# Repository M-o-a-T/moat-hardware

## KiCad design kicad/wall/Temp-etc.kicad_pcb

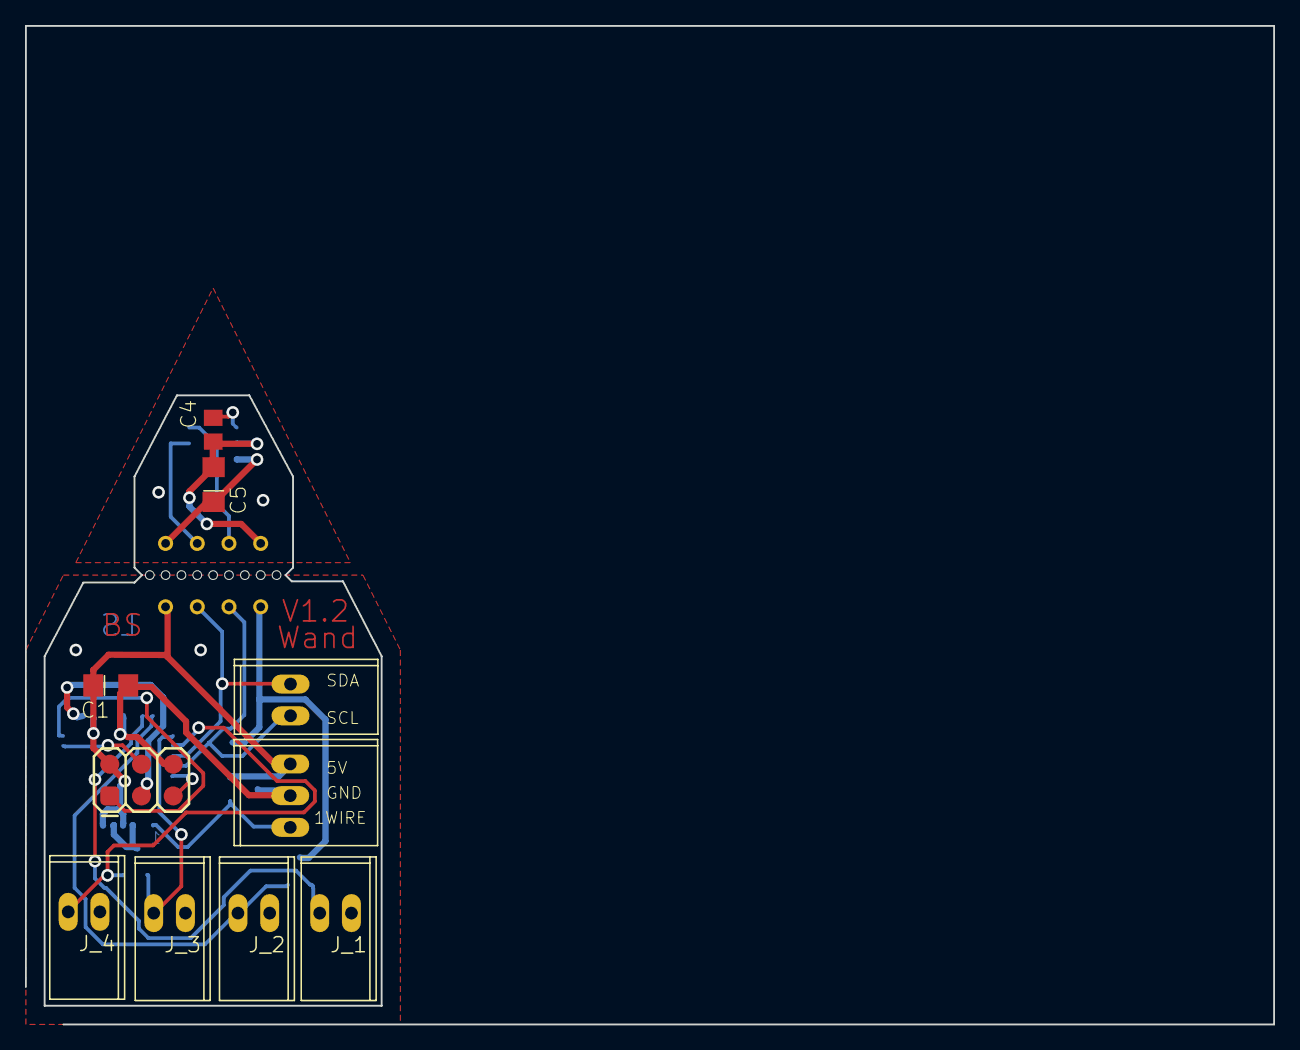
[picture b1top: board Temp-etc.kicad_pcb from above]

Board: 2 copper layers, 100.0 x 80.0 mm, 17 parts (0 on the bottom side), 18 nets.

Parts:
C1, C5: CP1206
C4: CC0805; C0805
D1, D4, D5, D6: ESD_DIODES; SOT23
IC1: MEGA8-PTQFP; TQFP32-08
JP1: PINHD-1X2LEVER; 1X02_GN
JP2: PINHD-2X4BRIDGE; 2X04_BRIDGE
J_1, J_2, J_3, J_4: PINHD-1X2LEVER; 1X02_GN
LEVER1: PINHD-1X3LEVER; 1X03_GN
U$1: AVR_SPI_PRG_6PAD; 2X3_PAD
U$2: CHIPCAP2

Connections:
/B1: D4.1, IC1.23, J_1.2
/B2: D4.2, IC1.24, J_2.2
/B3: D5.1, IC1.25, J_3.2
/B4: D5.2, IC1.26, J_4.2
/SCL: D6.2, IC1.28, JP1.2, JP2.4
/SDA: D6.1, IC1.27, JP1.1, JP2.6
GND: C1.-, D1.3, D4.3, D5.3, D6.3, IC1.3, IC1.5, IC1.21, JP2.2, J_1.1, J_2.1, J_3.1, J_4.1, LEVER1.2, U$1.P$6
unnamed: C4.1, C5.-, JP2.1, U$2.P$6
unnamed: C4.2, U$2.P$5
unnamed: C5.+, JP2.7, U$2.P$7
unnamed: D1.1, IC1.1, LEVER1.3
unnamed: IC1.15, U$1.P$4
unnamed: IC1.16, U$1.P$1
unnamed: IC1.17, U$1.P$3
unnamed: IC1.29, U$1.P$5
unnamed: JP2.3, U$2.P$4
unnamed: JP2.5, U$2.P$3
VCC: C1.+, D1.2, IC1.4, IC1.6, IC1.18, JP2.8, LEVER1.1, U$1.P$2

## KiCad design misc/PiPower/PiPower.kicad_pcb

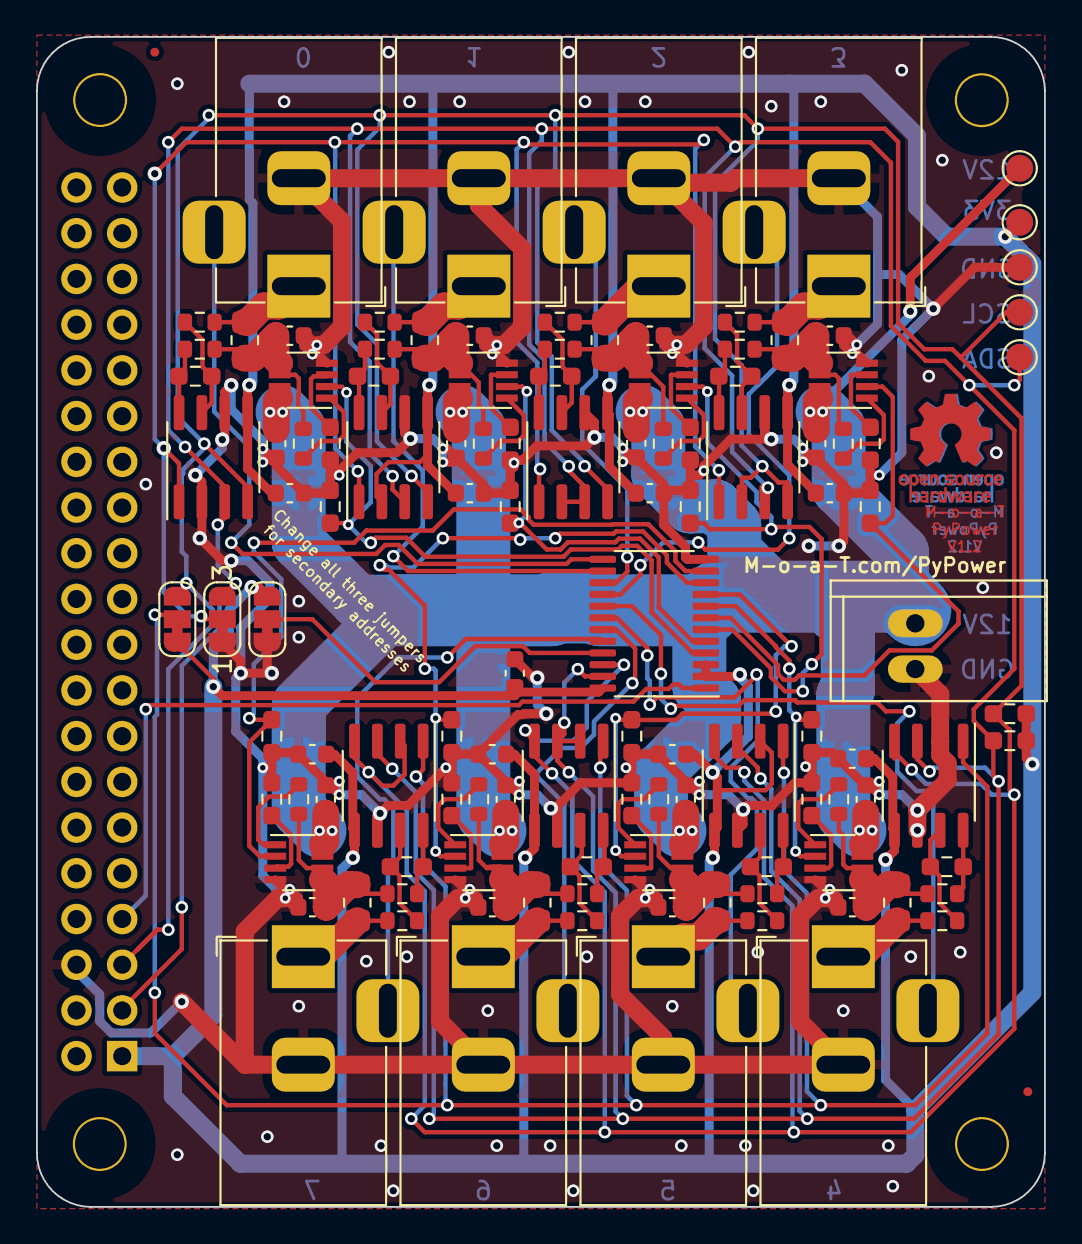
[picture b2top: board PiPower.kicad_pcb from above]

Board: 2 copper layers, 56.0 x 65.0 mm, 122 parts (1 on the bottom side), 73 nets.

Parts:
C1, C3, C6, C7, C9, C12, C13, C15, C17, C23, C26, C27, C30, C32, C33, C36: 10µF; C_0603_1608Metric
C2, C8, C10, C11, C18, C28, C29, C31: 0; R_0603_1608Metric_Pad0.98x0.95mm_HandSolder
C4, C14, C16, C19, C24, C34, C35, C37, C41: .1µF; C_0603_1608Metric
C5, C20, C21, C22, C25, C38, C39, C40: 1µ; R_0603_1608Metric_Pad0.98x0.95mm_HandSolder
H1, H2, H3, H4: 3mm_Mounting_Hole; NPTH_3mm_ID
J1: Raspberry_Pi_2_3; PinSocket_2x20_P2.54mm_Vertical
J2: Power; 1X02_GN
J3: Out 0; Barrel Jack locking
J4: Out 1; Barrel Jack locking
J5: Out 2; Barrel Jack locking
J6: Out 3; Barrel Jack locking
J7: Out 4; Barrel Jack locking
J8: Out 5; Barrel Jack locking
J9: Out 7; Barrel Jack locking
J10: Out 6; Barrel Jack locking
JP1, JP2, JP3: Jumper_3_Bridged12; SolderJumper-3_P1.3mm_Bridged12_RoundedPad1.0x1.5mm_NumberL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
R1, R5, R6, R7, R17, R21, R22, R23: 22; R_0603_1608Metric
R2, R4, R8, R10, R11, R13, R14, R16, R18, R20, R24, R25, R28, R29, R30, R32: 10; R_0603_1608Metric
R3, R9, R12, R15, R19, R26, R27, R31: .1; R_0805_2012Metric_Pad1.20x1.40mm_HandSolder
R33, R34: 1k; R_0603_1608Metric_Pad0.98x0.95mm_HandSolder
R35, R36, R37, R38, R39, R40, R41, R42: 10k; R_0603_1608Metric_Pad0.98x0.95mm_HandSolder
TP1, TP2, TP3, TP4, TP5: TestPoint; TestPoint_Pad_D1.5mm
U1, U3, U4, U5, U8, U11, U12, U13: MP5014A; TSOT-23-8
U2, U6, U7, U9, U10, U14, U15, U16: INA219AxD; SOIC-8_3.9x4.9mm_P1.27mm
U17: PCAL6416APW; TSSOP-24_4.4x7.8mm_P0.65mm

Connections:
+3V3: C4.1, C14.1, C16.1, C19.1, C24.1, C34.1, C35.1, C37.1, C41.1, J1.1 (3V3), JP2.1 (A), JP3.3 (B), R33.2, R34.2, TP2.1, U2.5 (VS), U6.2 (A0), U6.5 (VS), U7.5 (VS), U9.5 (VS), U10.5 (VS), U14.2 (A0), U14.5 (VS), U15.5 (VS), U16.5 (VS), U17.2 (VDD_I2C), U17.3 (~RESET), U17.24 (VDD_P)
+12V: C1.1, C6.1, C7.1, C9.1, C13.1, C26.1, C27.1, C30.1, J2.1, TP3.1, U1.7 (Vcc), U1.8 (Vcc), U3.7 (Vcc), U3.8 (Vcc), U4.7 (Vcc), U4.8 (Vcc), U5.7 (Vcc), U5.8 (Vcc), U8.7 (Vcc), U8.8 (Vcc), U11.7 (Vcc), U11.8 (Vcc), U12.7 (Vcc), U12.8 (Vcc), U13.7 (Vcc), U13.8 (Vcc)
/The other seven/V12O1: J4.1, R9.2, R11.2
/The other seven/V12O2: J5.1, R12.2, R14.2
/The other seven/V12O3: J6.1, R15.2, R16.2
/The other seven/V12O4: J7.1, R19.2, R20.2
/The other seven/V12O5: J8.1, R26.2, R28.2
/The other seven/V12O6: J10.1, R31.2, R32.2
/The other seven/V12O7: J9.1, R27.2, R29.2
/The other seven/V12P1: C12.1, R5.2, R8.2, R9.1, U3.5 (Source), U3.6 (Source)
/The other seven/V12P2: C15.1, R6.2, R10.2, R12.1, U4.5 (Source), U4.6 (Source)
/The other seven/V12P3: C17.1, R7.2, R13.2, R15.1, U5.5 (Source), U5.6 (Source)
/The other seven/V12P4: C23.1, R17.2, R18.2, R19.1, U8.5 (Source), U8.6 (Source)
/The other seven/V12P5: C32.1, R21.2, R24.2, R26.1, U11.5 (Source), U11.6 (Source)
/The other seven/V12P6: C36.1, R23.2, R30.2, R31.1, U13.5 (Source), U13.6 (Source)
/V12O0: J3.1, R3.2, R4.2
/V12P0: C3.1, R1.2, R2.2, R3.1, U1.5 (Source), U1.6 (Source)
ENA0: R42.2, U1.2 (Enable/Fault), U17.4 (P0_0)
ENA1: R41.2, U3.2 (Enable/Fault), U17.5 (P0_1)
ENA2: R40.2, U4.2 (Enable/Fault), U17.6 (P0_2)
ENA3: R39.2, U5.2 (Enable/Fault), U17.7 (P0_3)
ENA4: R38.2, U8.2 (Enable/Fault), U17.8 (P0_4)
ENA5: R37.2, U11.2 (Enable/Fault), U17.9 (P0_5)
ENA6: R36.2, U13.2 (Enable/Fault), U17.10 (P0_6)
ENA7: R35.2, U12.2 (Enable/Fault), U17.11 (P0_7)
GND: C1.2, C2.2, C3.2, C4.2, C6.2, C7.2, C8.2, C9.2, C10.2, C11.2, C12.2, C13.2, C14.2, C15.2, C16.2, C17.2, C18.2, C19.2, C23.2, C24.2, C26.2, C27.2, C28.2, C29.2, C30.2, C31.2, C32.2, C33.2, C34.2, C35.2, C36.2, C37.2, C41.2, J1.6 (GND), J2.2, J3.2, J4.2, J5.2, J6.2, J7.2, J8.2, J9.2, J10.2, JP1.1 (A), JP3.1 (A), R35.1, R36.1, R37.1, R38.1, R39.1, R40.1, R41.1, R42.1, TP1.1, U1.4 (GND), U2.2 (A0), U2.6 (GND), U3.4 (GND), U4.4 (GND), U5.4 (GND), U6.6 (GND), U7.6 (GND), U8.4 (GND), U9.6 (GND), U10.2 (A0), U10.6 (GND), U11.4 (GND), U12.4 (GND), U13.4 (GND), U14.6 (GND), U15.6 (GND), U16.6 (GND), U17.12 (VSS)
unnamed: C2.1, U1.3 (DV/DT)
unnamed: C5.1, R2.1, U2.8 (IN+)
unnamed: C5.2, R4.1, U2.7 (IN-)
unnamed: C8.1, U3.3 (DV/DT)
unnamed: C10.1, U4.3 (DV/DT)
unnamed: C11.1, U5.3 (DV/DT)
unnamed: C18.1, U8.3 (DV/DT)
unnamed: C20.1, R8.1, U6.8 (IN+)
unnamed: C20.2, R11.1, U6.7 (IN-)
unnamed: C21.1, R10.1, U7.8 (IN+)
unnamed: C21.2, R14.1, U7.7 (IN-)
unnamed: C22.1, R13.1, U9.8 (IN+)
unnamed: C22.2, R16.1, U9.7 (IN-)
unnamed: C25.1, R18.1, U10.8 (IN+)
unnamed: C25.2, R20.1, U10.7 (IN-)
unnamed: C28.1, U11.3 (DV/DT)
unnamed: C29.1, U12.3 (DV/DT)
unnamed: C31.1, U13.3 (DV/DT)
unnamed: C33.1, R22.2, R25.2, R27.1, U12.5 (Source), U12.6 (Source)
unnamed: C38.1, R24.1, U14.8 (IN+)
unnamed: C38.2, R28.1, U14.7 (IN-)
unnamed: C39.1, R25.1, U15.8 (IN+)
unnamed: C39.2, R29.1, U15.7 (IN-)
unnamed: C40.1, R30.1, U16.8 (IN+)
unnamed: C40.2, R32.1, U16.7 (IN-)
unnamed: J1.7 (GCLK0/GPIO4), U17.1 (~INT)
unnamed: R1.1, U1.1 (I-Limit)
unnamed: R5.1, U3.1 (I-Limit)
unnamed: R6.1, U4.1 (I-Limit)
unnamed: R7.1, U5.1 (I-Limit)
unnamed: R17.1, U8.1 (I-Limit)
unnamed: R21.1, U11.1 (I-Limit)
unnamed: R22.1, U12.1 (I-Limit)
unnamed: R23.1, U13.1 (I-Limit)
SCL: J1.5 (SCL/GPIO3), JP2.3 (B), R33.1, TP4.1, U2.4 (SCL), U6.4 (SCL), U7.4 (SCL), U9.2 (A0), U9.4 (SCL), U10.4 (SCL), U14.4 (SCL), U15.2 (A0), U15.4 (SCL), U16.4 (SCL), U17.22 (SCL)
SDA: J1.3 (SDA/GPIO2), JP1.3 (B), R34.1, TP5.1, U2.3 (SDA), U6.3 (SDA), U7.2 (A0), U7.3 (SDA), U9.3 (SDA), U10.3 (SDA), U14.3 (SDA), U15.3 (SDA), U16.2 (A0), U16.3 (SDA), U17.23 (SDA)
SEL: JP3.2 (C), U17.21 (ADDR)
SEL03: JP1.2 (C), U2.1 (A1), U6.1 (A1), U7.1 (A1), U9.1 (A1)
SEL47: JP2.2 (C), U10.1 (A1), U14.1 (A1), U15.1 (A1), U16.1 (A1)
SENS0: J3.3, U17.13 (P1_0)
SENS1: J4.3, U17.14 (P1_1)
SENS2: J5.3, U17.15 (P1_2)
SENS3: J6.3, U17.16 (P1_3)
SENS4: J7.3, U17.17 (P1_4)
SENS5: J8.3, U17.18 (P1_5)
SENS6: J10.3, U17.19 (P1_6)
SENS7: J9.3, U17.20 (P1_7)

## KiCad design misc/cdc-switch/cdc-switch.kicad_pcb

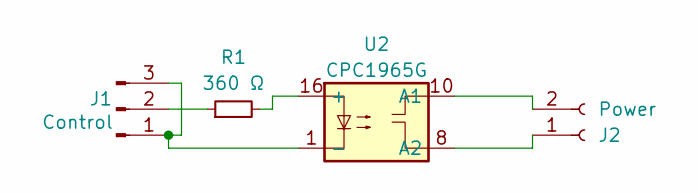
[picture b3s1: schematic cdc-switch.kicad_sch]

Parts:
J1: Control; PinHeader_1x03_P2.54mm_Horizontal
J2: Power; Conn_P5.1mm_2_Molex
R1: R_220_0603; R_0603_1608Metric_Pad0.98x0.95mm_HandSolder
U2: CPC1965G; DIL16-CPC1965G

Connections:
unnamed: J1.1, J1.3, U2.1 (-)
unnamed: J1.2, R1.1
unnamed: J2.1, U2.8 (A2)
unnamed: J2.2, U2.10 (A1)
unnamed: R1.2, U2.16 (+)

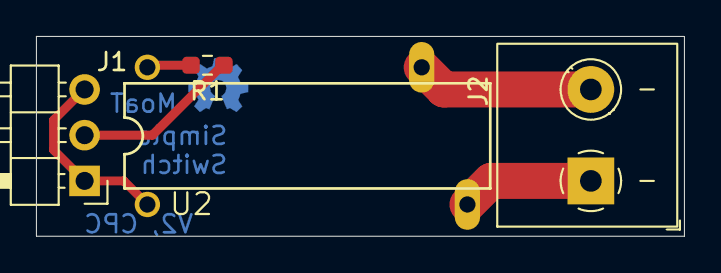
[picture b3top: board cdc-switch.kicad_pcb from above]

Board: 2 copper layers, 36.0 x 11.1 mm, 4 parts (0 on the bottom side), 5 nets.

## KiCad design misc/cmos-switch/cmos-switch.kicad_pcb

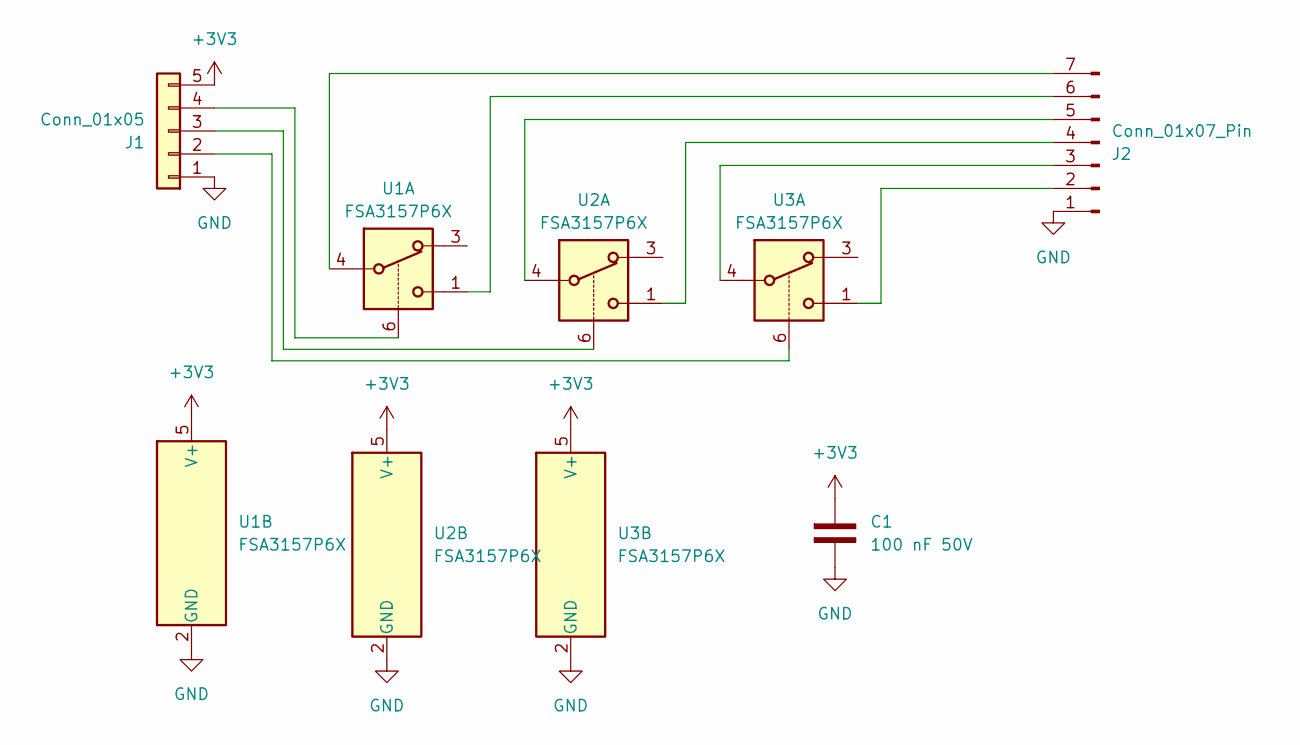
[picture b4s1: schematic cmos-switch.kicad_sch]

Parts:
C1: CP_100n_50V_0603; C_0603_1608Metric; LCSC C14663
J1: Conn_01x05; PinHeader_1x05_P2.54mm_Vertical
J2: Conn_01x07_Pin; PinHeader_1x07_P2.54mm_Vertical
U1, U2, U3: FSA3157P6X; SOT-363_SC-70-6

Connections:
+3V3: C1.1, J1.5, U1.5 (V+), U2.5 (V+), U3.5 (V+)
GND: C1.2, J1.1, J2.1, U1.2 (GND), U2.2 (GND), U3.2 (GND)
unnamed: J1.2, U3.6
unnamed: J1.3, U2.6
unnamed: J1.4, U1.6
unnamed: J2.2, U3.1
unnamed: J2.3, U3.4
unnamed: J2.4, U2.1
unnamed: J2.5, U2.4
unnamed: J2.6, U1.1
unnamed: J2.7, U1.4

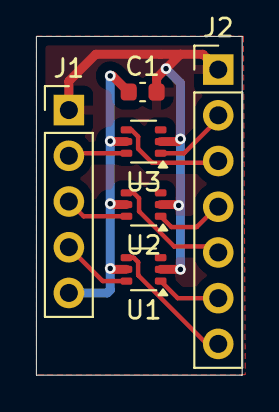
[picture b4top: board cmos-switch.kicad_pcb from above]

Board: 2 copper layers, 11.4 x 18.8 mm, 6 parts (0 on the bottom side), 11 nets.

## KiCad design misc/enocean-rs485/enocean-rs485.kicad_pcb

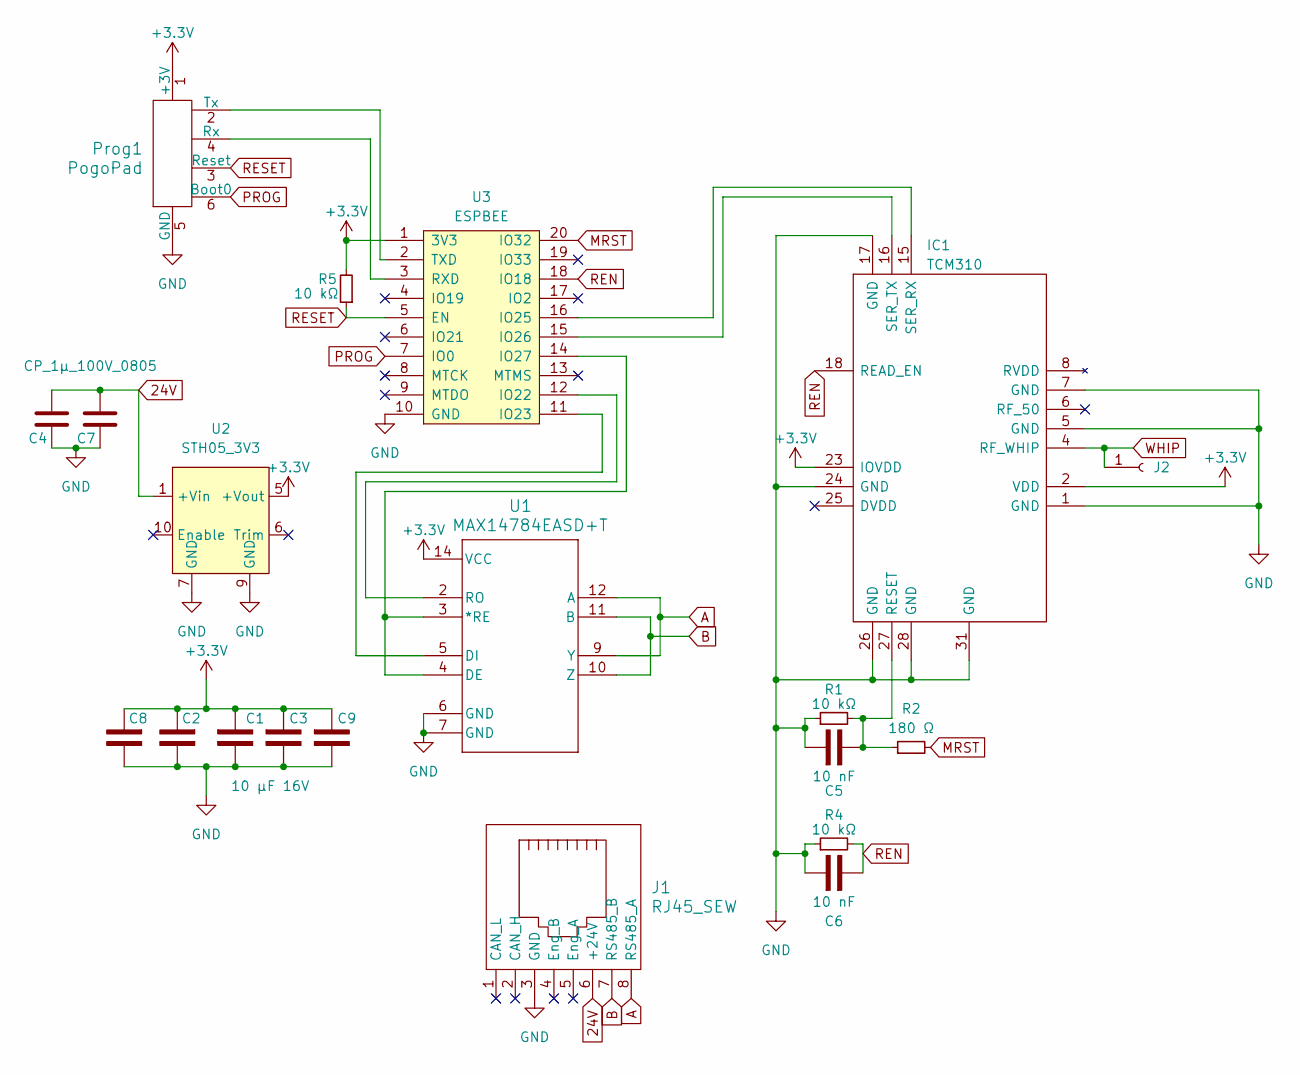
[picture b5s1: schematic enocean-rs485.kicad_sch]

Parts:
C1, C2, C3, C8, C9: CP_10µ_16V_0603; C_0603_1608Metric
C4, C7: CP_1µ_100V_0805; R_0805_2012Metric; Farnell 3243166
C5, C6: C_10n_0603; C_0603_1608Metric
IC1: TCM310; Manufacturer_Part_Number TCM310
J1: RJ45_SEW; RJ45-NO-SHIELD
J2: Conn_01x01_Female; Pin_D0.7mm_L6.5mm_W1.8mm_FlatFork
Prog1: PogoPad; 2X3_PAD
R1, R4, R5: R_10k_0603; R_0603_1608Metric
R2: R_180_0603; R_0603_1608Metric
U1: MAX14784EASD+T; SO-16_3.9x9.9mm_P1.27mm
U2: STH05_3V3; STH05; Farnell 3212470
U3: ESPBEE

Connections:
24V: C4.1, C7.1, J1.6 (+24V), U2.1 (+Vin)
+3V3: C1.1, C2.1, C3.1, C8.1, C9.1, IC1.2 (VDD), IC1.23 (IOVDD), Prog1.1 (+3V), R5.2, U1.14 (VCC), U2.5 (+Vout), U3.1 (3V3)
A: J1.8 (RS485_A), U1.9 (Y), U1.12 (A)
B: J1.7 (RS485_B), U1.10 (Z), U1.11 (B)
GND: C1.2, C2.2, C3.2, C4.2, C5.1, C6.1, C7.2, C8.2, C9.2, IC1.1 (GND), IC1.5 (GND), IC1.7 (GND), IC1.17 (GND), IC1.24 (GND), IC1.26 (GND), IC1.28 (GND), IC1.31 (GND), J1.3 (GND), Prog1.5 (GND), R1.1, R4.1, U1.6 (GND), U1.7 (GND), U2.7 (GND), U2.9 (GND), U3.10 (GND)
MRST: R2.2, U3.20 (IO32)
unnamed: C5.2, IC1.27 (RESET), R1.2, R2.1
unnamed: IC1.15 (SER_RX), U3.16 (IO25)
unnamed: IC1.16 (SER_TX), U3.15 (IO26)
unnamed: Prog1.4 (Rx), U3.3 (RXD)
unnamed: Prog1.2 (Tx), U3.2 (TXD)
unnamed: U1.3 (*RE), U1.4 (DE), U3.14 (IO27)
unnamed: U1.5 (DI), U3.11 (IO23)
unnamed: U1.2 (RO), U3.12 (IO22)
PROG: Prog1.6 (Boot0), U3.7 (IO0)
REN: C6.2, IC1.18 (READ_EN), R4.2, U3.18 (IO18)
RESET: Prog1.3 (Reset), R5.1, U3.5 (EN)
WHIP: IC1.4 (RF_WHIP), J2.1

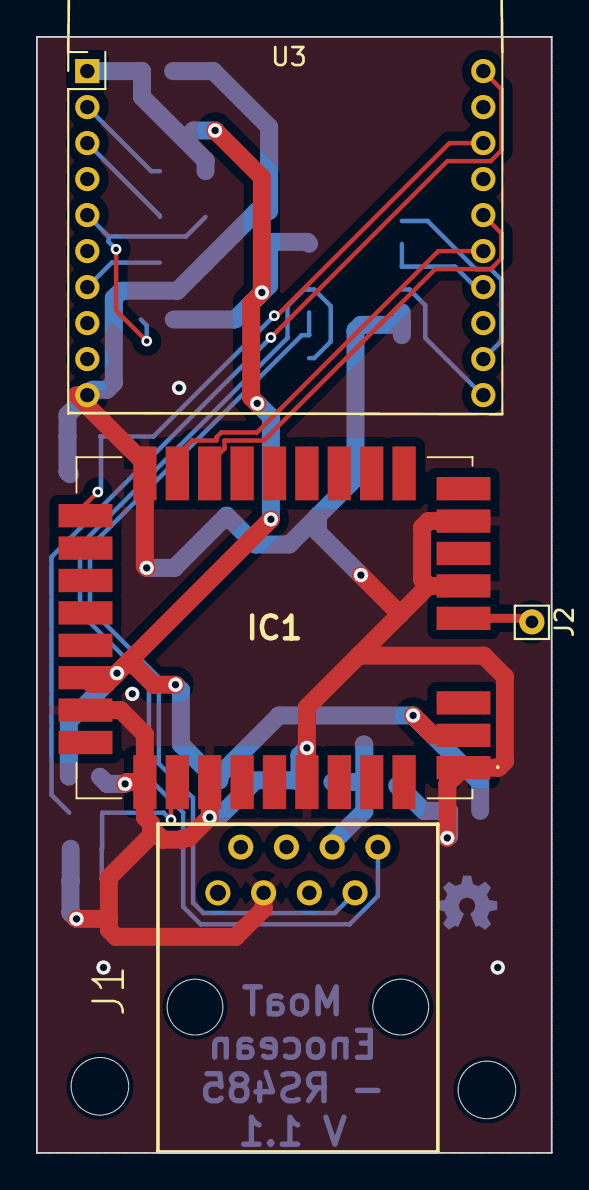
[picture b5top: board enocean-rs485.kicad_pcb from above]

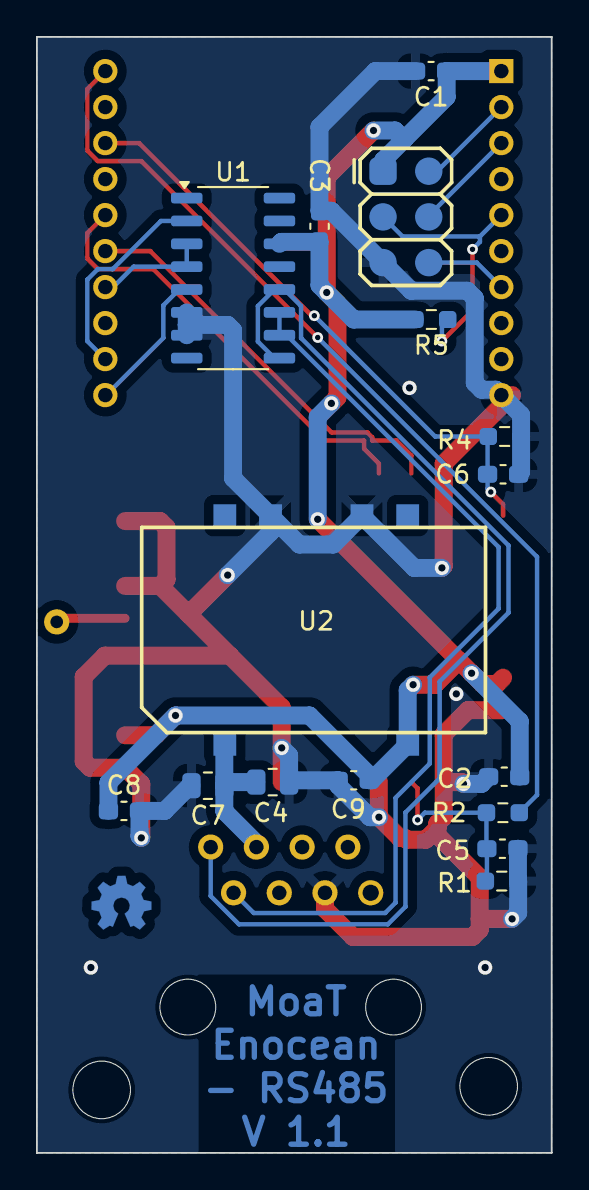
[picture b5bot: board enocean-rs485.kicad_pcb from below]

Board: 2 copper layers, 28.6 x 62.0 mm, 20 parts (16 on the bottom side), 18 nets.

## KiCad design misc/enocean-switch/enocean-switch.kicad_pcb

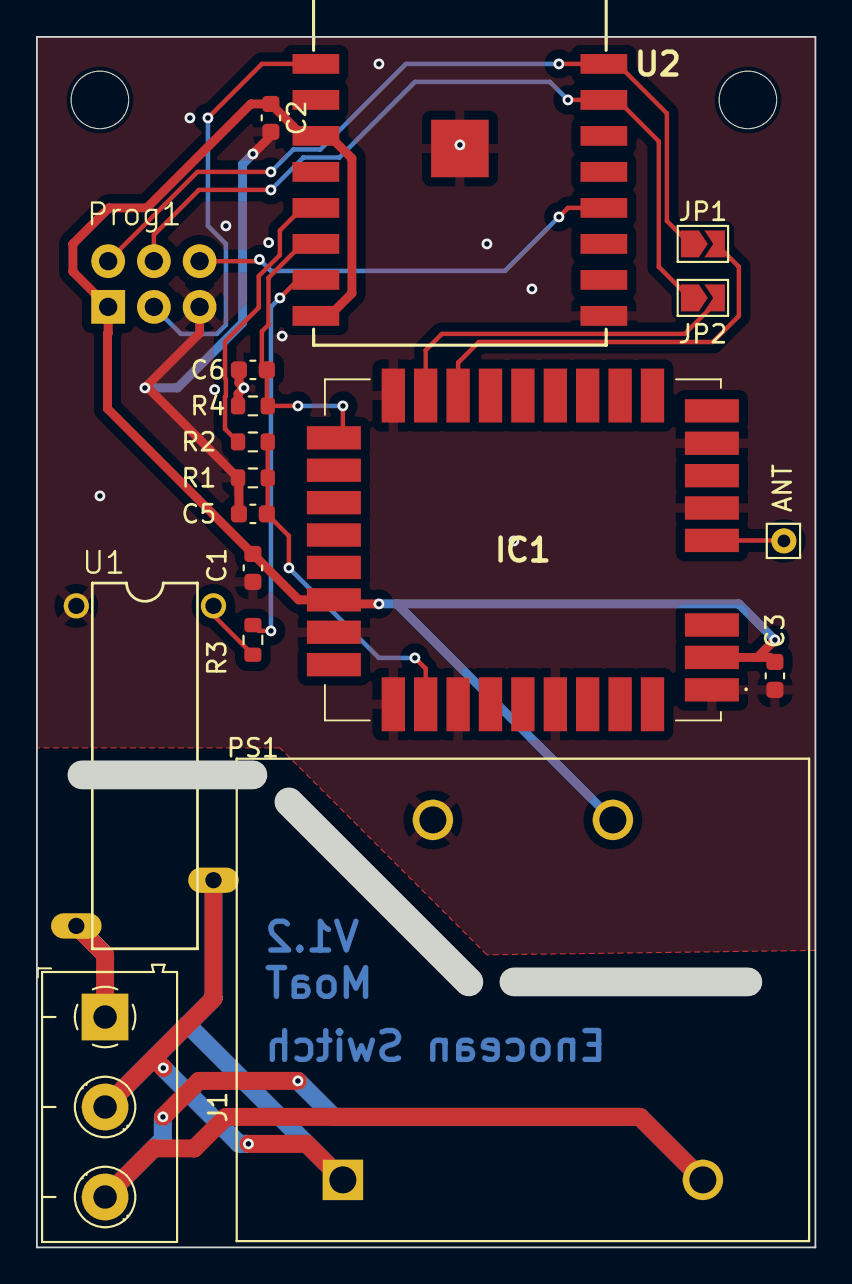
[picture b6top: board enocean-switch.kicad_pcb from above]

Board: 2 copper layers, 43.2 x 67.2 mm, 18 parts (0 on the bottom side), 17 nets.

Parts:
C1, C2, C3: CP_10µ_16V_0603; C_0603_1608Metric
C5, C6: C_10n_0603; C_0603_1608Metric
IC1: TCM310
J1: Conn_01x03_Female; Conn_P5.0mm_3_Lumberg
J2: Conn_01x01_Female; Pin_D0.7mm_L6.5mm_W1.8mm_FlatFork
JP1, JP2: Jumper_NC; SolderJumper-2_P1.3mm_Open_TrianglePad1.0x1.5mm
PS1: VTX-214-003-103; VTX-214
Prog1: PogoPad; 2X3-NS
R1, R4: R_10k_0603; R_0603_1608Metric
R2: R_180_0603; R_0603_1608Metric
R3: R_220_0603; R_0603_1608Metric
U1: CPC1965G; DIL16-CPC1965G
U2: ESP-12S

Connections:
+3V3: C1.1, C2.1, C3.1, IC1.2 (VDD), IC1.23 (IOVDD), PS1.3 (DC+), Prog1.1 (+3V), U2.3 (EN), U2.8 (VCC)
GND: C1.2, C2.2, C3.2, C5.1, C6.1, IC1.1 (GND), IC1.5 (GND), IC1.7 (GND), IC1.17 (GND), IC1.24 (GND), IC1.26 (GND), IC1.28 (GND), IC1.31 (GND), PS1.4 (DC-), Prog1.5 (GND), R1.1, R4.1, U1.1 (-), U2.9 (GND), U2.P$1 (GND)
MRST: R2.2, U2.5 (IO14)
unnamed: C5.2, IC1.27 (RESET), R1.2, R2.1
unnamed: IC1.15 (SER_RX), JP1.2
unnamed: IC1.16 (SER_TX), JP2.2
unnamed: J1.1, U1.8 (A2)
unnamed: J1.2, PS1.1 (L), U1.10 (A1)
unnamed: J1.3, PS1.2 (N)
unnamed: Prog1.3 (Reset), U2.1 (RST)
unnamed: JP2.1, Prog1.4 (Rx), U2.15 (RXD0)
unnamed: JP1.1, Prog1.2 (Tx), U2.16 (TXD0)
unnamed: R3.2, U1.16 (+)
PROG: Prog1.6 (Boot0), U2.12 (IO0)
REN: C6.2, IC1.18 (READ_EN), R4.2, U2.6 (IO12)
SIG: R3.1, U2.7 (IO13)
WHIP: IC1.4 (RF_WHIP), J2.1

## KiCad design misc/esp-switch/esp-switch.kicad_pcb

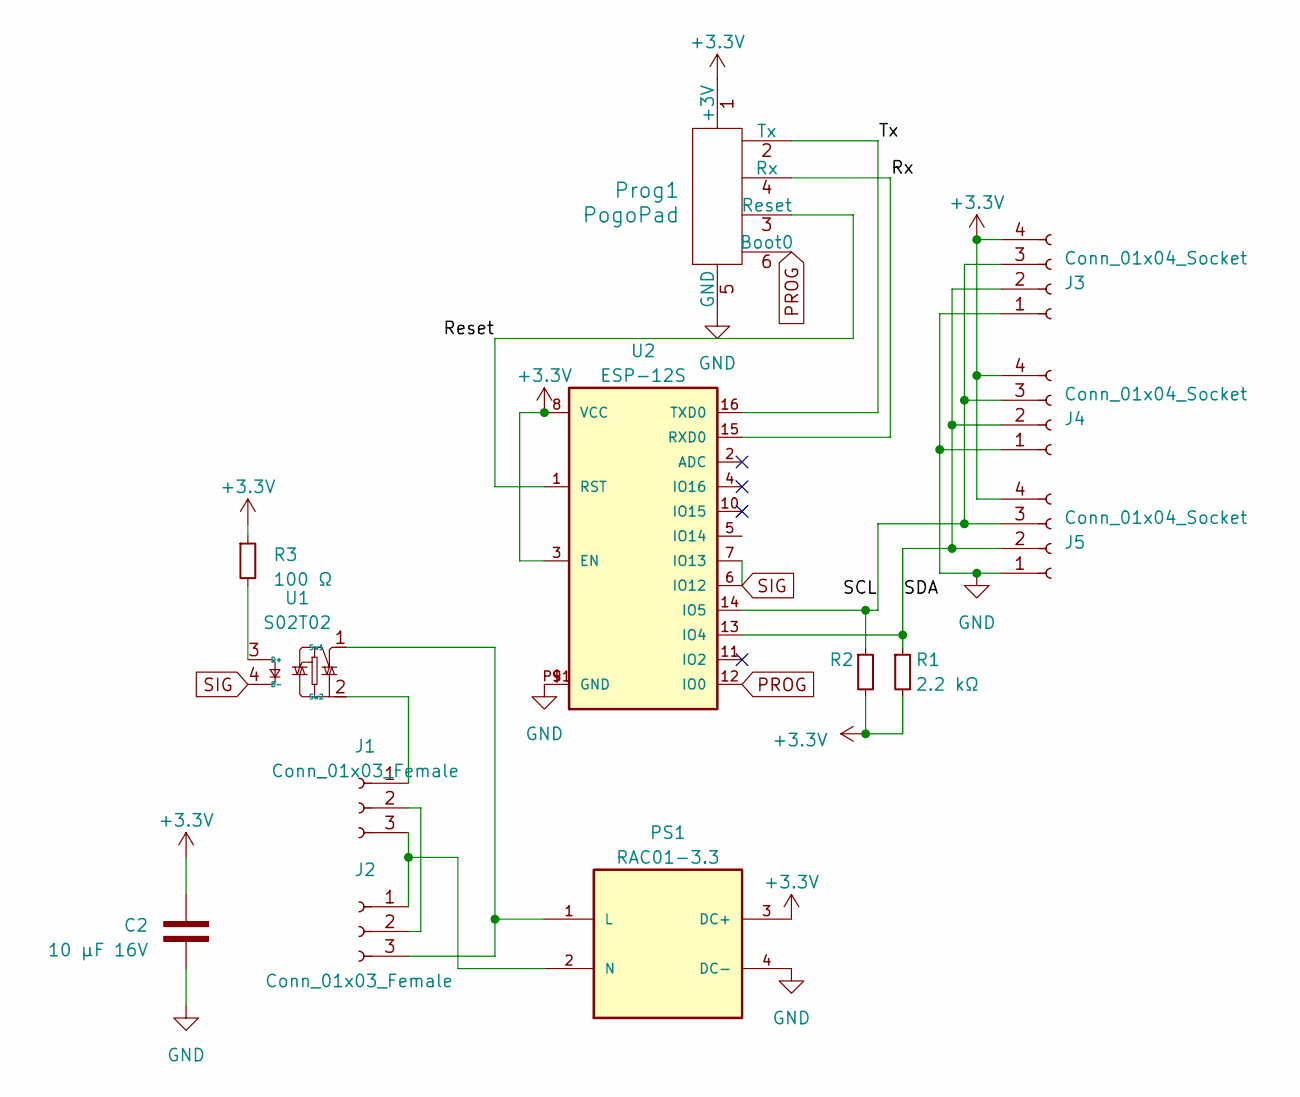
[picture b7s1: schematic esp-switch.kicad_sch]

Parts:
C2: CP_10µ_16V_0603; C_0603_1608Metric
J1, J2: Conn_01x03_Female; Conn_P5.0mm_3_Lumberg
J3, J4, J5: Conn_01x04_Socket; PinHeader_1x04_P2.54mm_Vertical
PS1: RAC01-3.3
Prog1: PogoPad; 2X3-NS
R1, R2: R_2k2_0603; R_0603_1608Metric
R3: R_220_0603; R_0603_1608Metric
U1: S02T02; S202T02
U2: ESP-12S

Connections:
+3V3: C2.1, J3.4, J4.4, J5.4, PS1.3 (DC+), Prog1.1 (+3V), R1.2, R2.2, R3.1, U2.3 (EN), U2.8 (VCC)
/Reset: Prog1.3 (Reset), U2.1 (RST)
/Rx: Prog1.4 (Rx), U2.15 (RXD0)
/SCL: J3.3, J4.3, J5.3, R2.1, U2.14 (IO5)
/SDA: J3.2, J4.2, J5.2, R1.1, U2.13 (IO4)
/Tx: Prog1.2 (Tx), U2.16 (TXD0)
GND: C2.2, J3.1, J4.1, J5.1, PS1.4 (DC-), Prog1.5 (GND), U2.9 (GND), U2.P$1 (GND)
unnamed: J1.1, U1.2 (Sw2)
unnamed: J1.2, J2.2
unnamed: J1.3, J2.1, PS1.2 (N)
unnamed: J2.3, PS1.1 (L), U1.1 (Sw1)
unnamed: R3.2, U1.3 (D+)
PROG: Prog1.6 (Boot0), U2.12 (IO0)
SIG: U1.4 (D-), U2.6 (IO12), U2.7 (IO13)

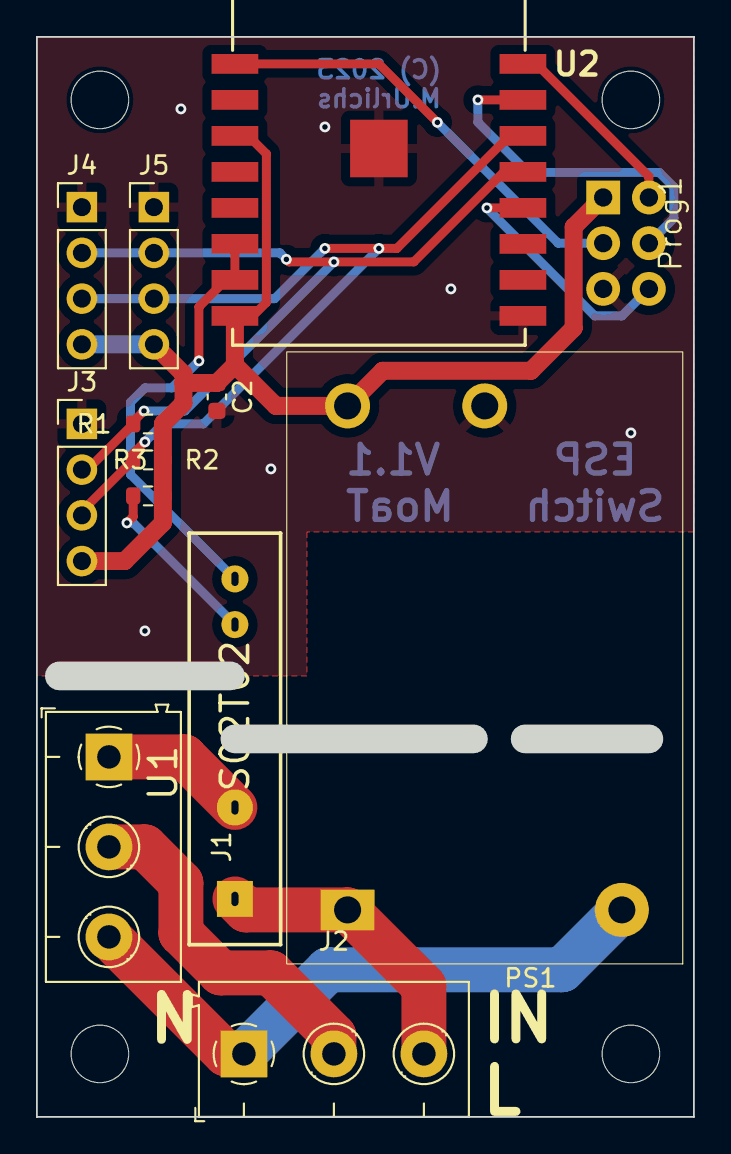
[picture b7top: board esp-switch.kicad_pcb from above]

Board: 2 copper layers, 36.5 x 60.0 mm, 13 parts (0 on the bottom side), 14 nets.

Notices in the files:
misc/esp-switch/esp-switch.kicad_pcb:
(C) 2023
